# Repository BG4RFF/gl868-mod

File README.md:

gl868-mod
=========

Telit GL868 GSM modem module.

Single-sided PCB:

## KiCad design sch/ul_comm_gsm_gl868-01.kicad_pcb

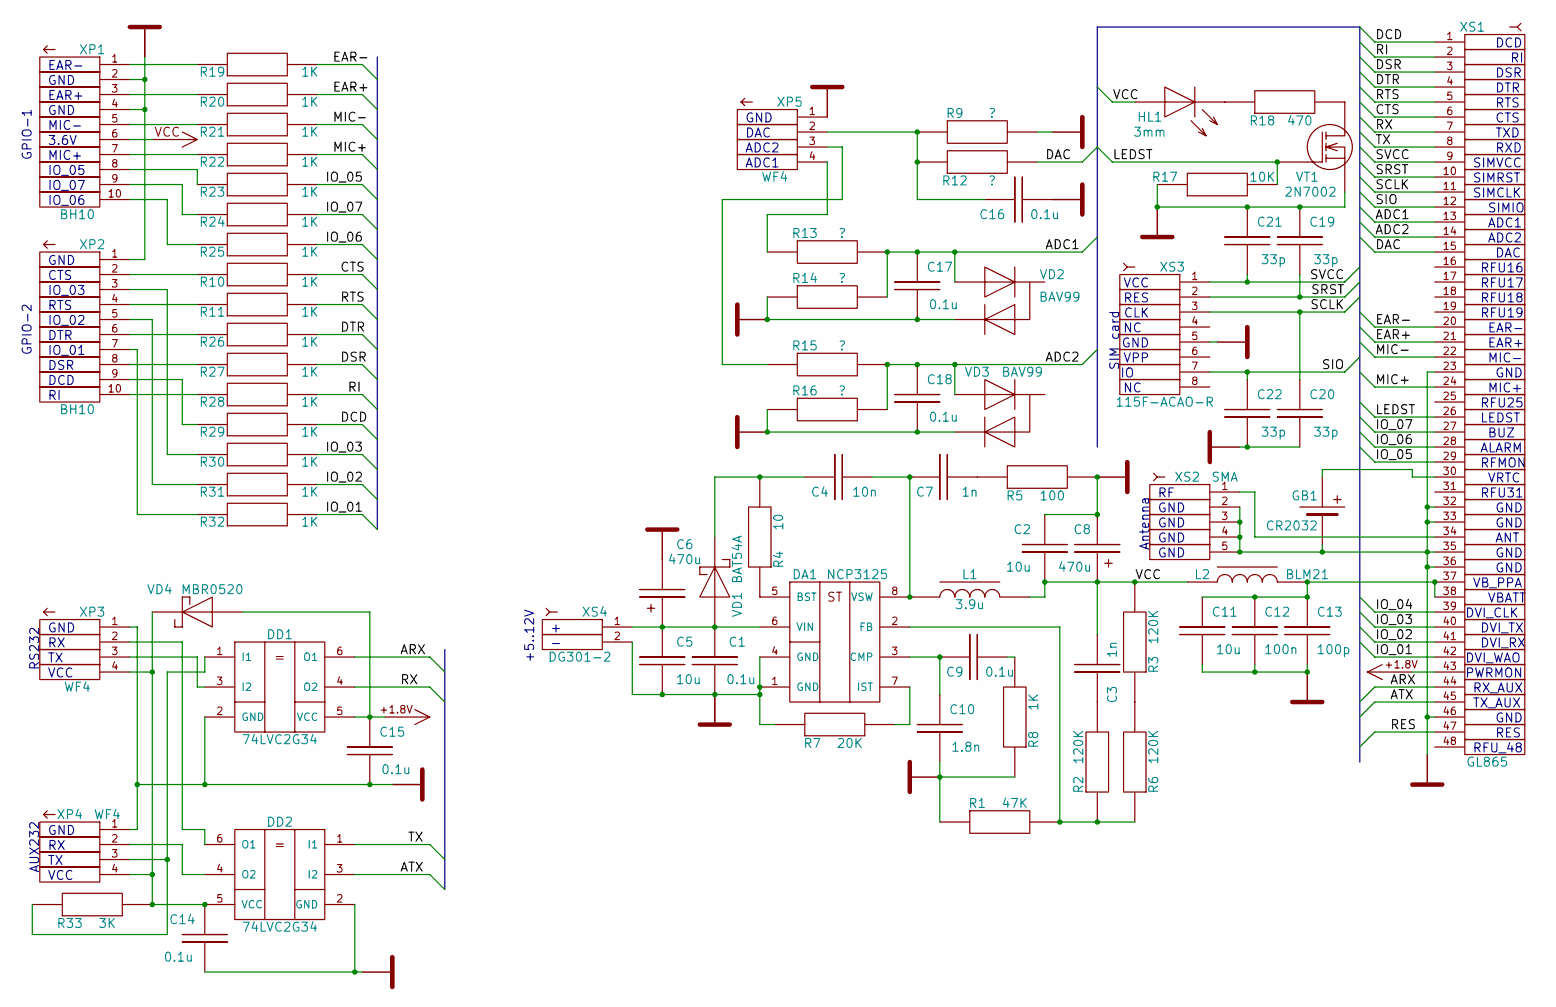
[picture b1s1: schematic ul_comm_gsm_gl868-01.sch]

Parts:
C1, C9, C14, C15, C16, C17, C18: 0.1u
C2, C5, C11: 10u
C3, C7: 1n
C4: 10n
C6, C8: 470u
C10: 1.8n
C12: 100n
C13: 100p
C19, C20, C21, C22: 33p
DA1: NCP3125
DD1, DD2: 74LVC2G34
GB1: CR2032
HL1: 3mm
L1: 3.9u
L2: BLM21
R1: 47K
R2, R3, R6: 120K
R4: 10
R5: 100
R7: 20K
R8, R10, R11, R19, R20, R21, R22, R23, R24, R25, R26, R27, R28, R29, R30, R31, R32: 1K
R9, R12, R13, R14, R15, R16: ?
R17: 10K
R18: 470
R33: 3K
VD1: BAT54A
VD2, VD3: BAV99
VD4: MBR0520
VT1: 2N7002
XP1, XP2: BH10
XP3, XP4, XP5: WF4
XS1: GL865
XS2: SMA
XS3: 115F-ACAO-R
XS4: DG301-2

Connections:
+1.8V: C15.1, DD1.5 (VCC), VD4.2, XS1.43
/ADC1: C17.1, R13.2, R14.2, VD2.1, XS1.13
/ADC2: C18.1, R15.2, R16.2, VD3.1, XS1.14
/ARX: DD1.6 (O1), XS1.44
/ATX: DD2.3 (I2), XS1.45
/CTS: R10.2, XS1.6
/DAC: R12.2, XS1.15
/DCD: R29.2, XS1.1
/DSR: R27.2, XS1.3
/DTR: R26.2, XS1.4
/EAR+: R20.2, XS1.21
/EAR-: R19.2, XS1.20
/IO_01: R32.2, XS1.42
/IO_02: R31.2, XS1.41
/IO_03: R30.2, XS1.40
/IO_04: XS1.39
/IO_05: R23.2, XS1.29
/IO_06: R25.2, XS1.28
/IO_07: R24.2, XS1.27
/LEDST: R17.2, VT1.1 (G), XS1.26
/MIC+: R22.2, XS1.24
/MIC-: R21.2, XS1.22
/RES: XS1.47
/RI: R28.2, XS1.2
/RTS: R11.2, XS1.5
/RX: DD1.4 (O2), XS1.7
/SCLK: C20.1, XS1.11, XS3.3
/SIO: C22.1, XS1.12, XS3.7
/SRST: C19.2, XS1.10, XS3.2
/SVCC: C21.2, XS1.9, XS3.1
/TX: DD2.1 (I1), XS1.8
GND: C1.2, C2.1, C5.2, C6.1, C8.1, C10.2, C11.2, C12.2, C13.2, C14.2, C15.2, C16.2, C17.2, C18.2, C19.1, C20.2, C21.1, C22.2, DA1.1 (GND), DA1.4 (GND), DD1.2 (GND), DD2.2 (GND), GB1.2 (-), R1.1, R5.2, R7.1, R8.1, R9.2, R14.1, R16.1, R17.1, VD2.3, VD3.3, VT1.3 (S), XP1.2, XP1.4, XP2.1, XP3.1, XP4.1, XP5.1, XS1.23, XS1.32, XS1.33, XS1.35, XS1.36, XS1.46, XS2.2, XS2.3, XS2.4, XS2.5, XS3.5, XS4.2
unnamed: C1.1, C5.1, C6.2, DA1.6 (VIN), VD1.2, XS4.1
unnamed: C3.1, R2.2
unnamed: C4.1, R4.2, VD1.1
unnamed: C4.2, C7.1, DA1.8 (VSW), L1.1
unnamed: C7.2, R5.1
unnamed: C9.2, R8.2
unnamed: C9.1, C10.1, DA1.3 (CMP)
unnamed: C11.1, C12.1, C13.1, L2.2, XS1.37, XS1.38
unnamed: C14.1, DD2.5 (VCC), R33.2, VD4.1, XP3.4, XP4.4
unnamed: C16.1, R9.1, R12.1, XP5.2
unnamed: DA1.2 (FB), R1.2, R2.1, R6.1
unnamed: DA1.5 (BST), R4.1
unnamed: DA1.7 (IST), R7.2
unnamed: DD1.1 (I1), R33.1, XP4.3
unnamed: DD1.3 (I2), XP3.3
unnamed: DD2.4 (O2), XP4.2
unnamed: DD2.6 (O1), XP3.2
unnamed: GB1.1 (+), XS1.30
unnamed: HL1.1, R18.1
unnamed: R3.1, R6.2
unnamed: R10.1, XP2.2
unnamed: R11.1, XP2.4
unnamed: R13.1, XP5.4
unnamed: R15.1, XP5.3
unnamed: R18.2, VT1.2 (D)
unnamed: R19.1, XP1.1
unnamed: R20.1, XP1.3
unnamed: R21.1, XP1.5
unnamed: R22.1, XP1.7
unnamed: R23.1, XP1.8
unnamed: R24.1, XP1.9
unnamed: R25.1, XP1.10
unnamed: R26.1, XP2.6
unnamed: R27.1, XP2.8
unnamed: R28.1, XP2.10
unnamed: R29.1, XP2.9
unnamed: R30.1, XP2.3
unnamed: R31.1, XP2.5
unnamed: R32.1, XP2.7
unnamed: XS1.34, XS2.1

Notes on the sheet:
DCD
DSR
DTR
RTS
CTS
TXD
RXD
SIMVCC
SIMRST
SIMCLK
SIMIO
ADC1
ADC2
DAC
RFU16
RFU17
RFU18
RFU19
EAR-
EAR+
MIC-
GND
MIC+
RFU25
LEDST
BUZ
ALARM
RFMON
VRTC
RFU31
ANT
VB_PPA
VBATT
DVI_CLK
DVI_TX
DVI_RX
DVI_WAO
PWRMON
RX_AUX
TX_AUX

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
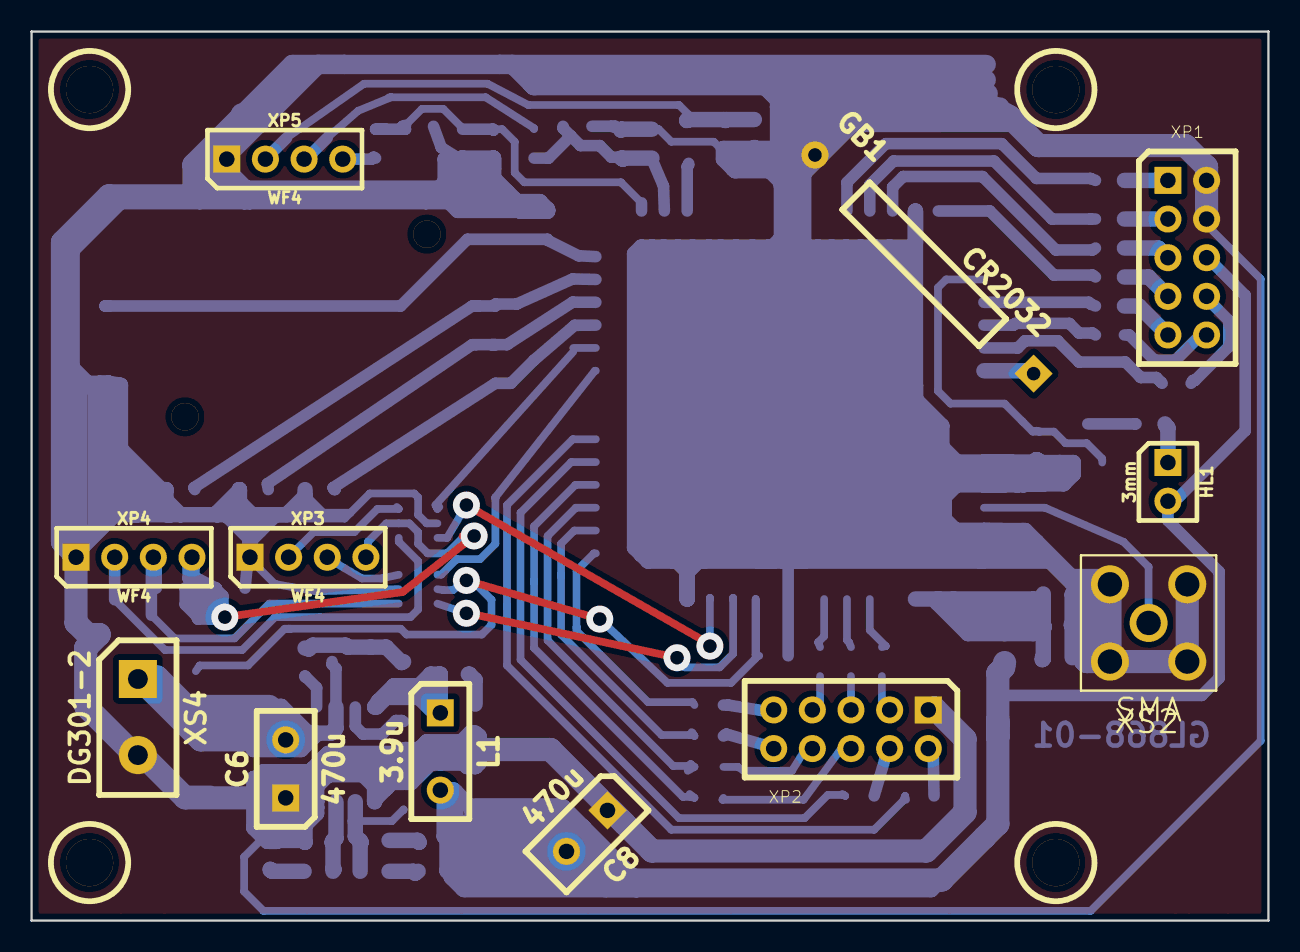
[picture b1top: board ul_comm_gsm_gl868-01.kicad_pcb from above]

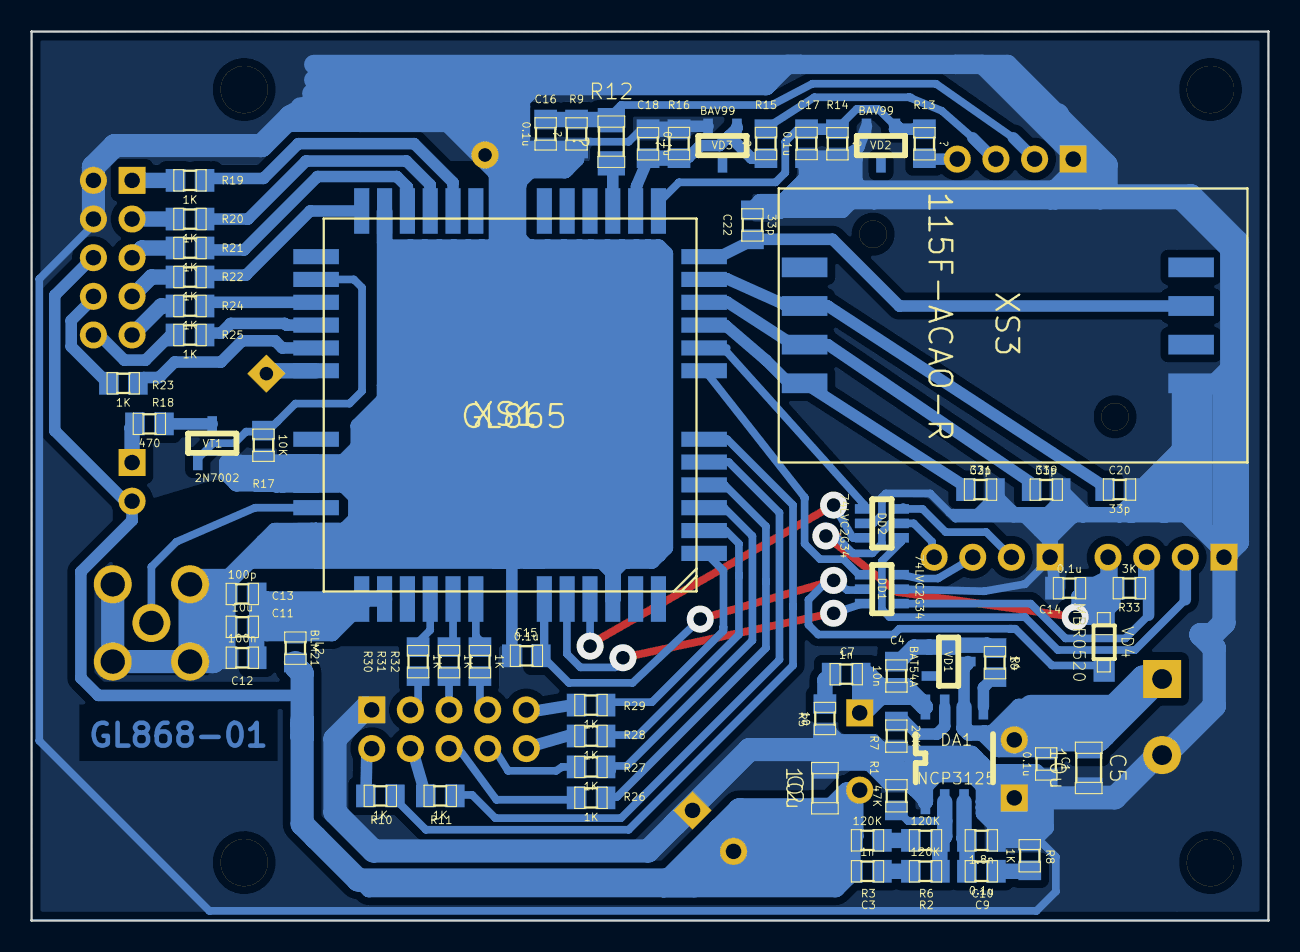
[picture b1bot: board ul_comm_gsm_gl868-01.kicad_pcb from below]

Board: 2 copper layers, 81.3 x 58.4 mm, 80 parts (64 on the bottom side), 71 nets.

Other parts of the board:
REF: VAL**; SIP_1_3.1mm
REF#2, REF#3, REF#4: VAL**; SIP_1_3.1mm

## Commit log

2014-09-10 start
2014-09-10 none
